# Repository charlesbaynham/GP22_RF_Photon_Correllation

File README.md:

README
======

This is the source code for the driver for the GP22 TDC chip eval board, programmed by Charles Baynham.

It is written in c++ and can be compiled and uploaded via the Arduino IDE. This code is intended to run on an Arduino Due (or other 3.3V Arduino board) to act as an interface to the GP22. When running, the Arduino will setup the GP22 with whatever configuration is stored in the GP22's EEPROM then wait for simple commands. 

N.B. The configuration of the GP22 is done via the software interface provided on http://ACAM.de. In particular, be cautious of the DELVAL1 setting in "Ultrasonic Time of Flight". This setting should be zero, but isn't by default. If not corrected, this will greatly limit the resolution of the device. 

_IMPORTANT_
-----------

If you loaded this from the T: drive you may not have the latest version. This directory is a GIT repository and so contains a hidden folder called `.git` that has a record of every change made to this code since conception. In order to use this you must install a git client. https://windows.github.com/ is a simple one or http://www.sourcetreeapp.com/ is more full-featured. 

Once installed, "checkout" the master branch for the latest code version.

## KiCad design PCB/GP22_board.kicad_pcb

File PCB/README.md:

NPL Backplane
=============

Usage
-----

_This is a Kicad Template: this whole folder should be copied into your "...\Documents\kicad\template\" folder. It can then be used be starting a new Kicad project with the "New Project from Template (Ctrl+T)" option._

Child board template - v1.0
---------------------------

This project template is designed for projects intending to use the NPL backplane system.

The NPL backplane supports 100x100mm boards and provides various supply voltages, as well as 30 GPIO ports and an interface for RS485 - serial communication. Protocol implementation is outside the scope of this document, but the Modbus protocol is recommended.

Power lines are not guaranteed to be quiet so noise-senstive applications should implement their own filtering or use an external supply. Maximum current draw is t.b.c. but other than the +15V supply line, other power supplies are expected to be relatively low current; intended for powering signal circuits only.

For more information, please contact Charles Baynham

(c) 2016 Charles Baynham

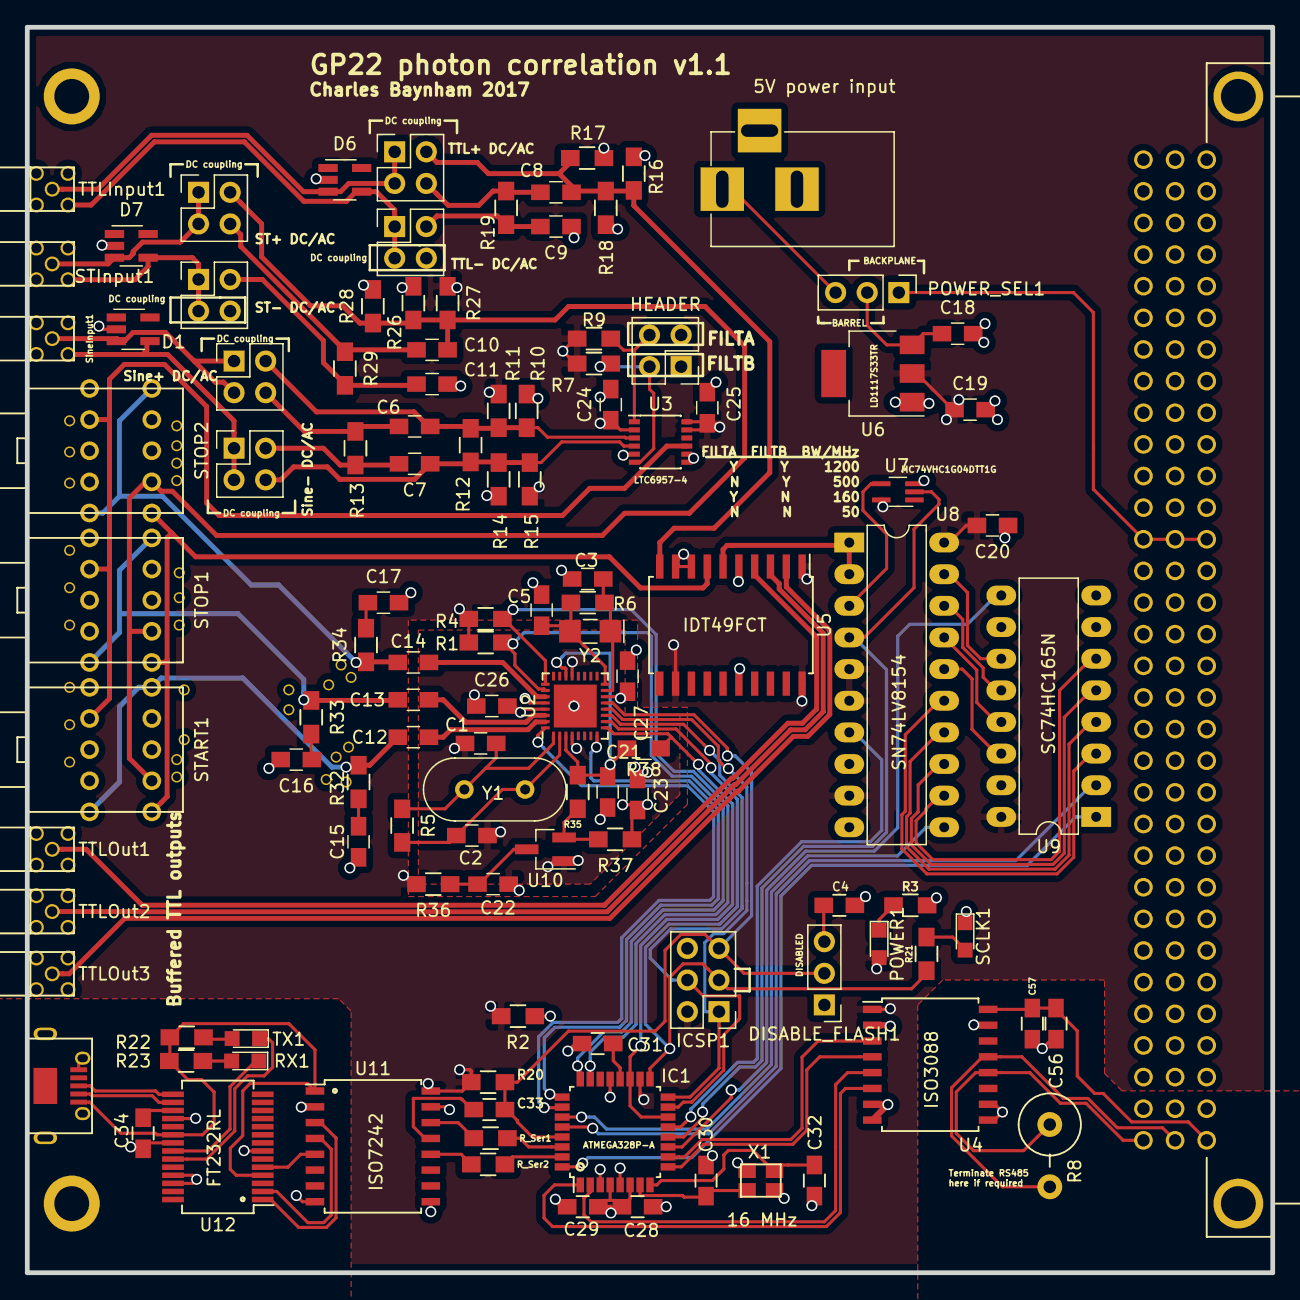
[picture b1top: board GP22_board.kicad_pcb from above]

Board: 4 copper layers, 100.0 x 100.0 mm, 145 parts (0 on the bottom side), 108 nets.

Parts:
C1, C2, C3, C5: 3p3; C_0805_HandSoldering
C4, C18, C28, C56: 1u; C_0805_HandSoldering
C6, C7, C8, C9, C10, C11: C_Small; C_0805_HandSoldering
C12, C13, C14: 10n; C_0805_HandSoldering
C15, C16, C17: x; C_0805_HandSoldering
C19: 10u; C_0805_HandSoldering
C20, C24, C25, C26, C27, C29, C31, C33, C34, C57: 100n; C_0805_HandSoldering
C21, C23: 33u; C_0805_HandSoldering
C22: 4u7; C_0805_HandSoldering
C30, C32: 8p; C_0805_HandSoldering
CON1: 5V power input; BARREL_JACK
D1, D6, D7: ESDA5V3SC6; SOT-23-5_HandSoldering
DISABLE_FLASH1: JMP; Pin_Header_Straight_1x03_Pitch2.54mm
FILT_SEL1: HEADER; Pin_Header_Straight_2x02_Pitch2.54mm
IC1: ATMEGA328P-A; LQFP-32_7x7mm_Pitch0.8mm
ICSP1: HEADER; Pin_Header_Straight_2x03_Pitch2.54mm
P4: USB_OTG; MICRO-B_USB_TOP_MOUNT
P7, P8, P9, P10, P11, P12: HEADER; Pin_Header_Straight_2x02_Pitch2.54mm
POWER1: LED; LED_0805
POWER_SEL1: JMP; Pin_Header_Straight_1x03_Pitch2.54mm
R1, R2, R4: 2M; R_0805_HandSoldering
R3, R21, R22, R23: 100R; R_0805_HandSoldering
R5: 1M; R_0805_HandSoldering
R6: x; R_0805_HandSoldering
R7, R9: 100k; R_0805_HandSoldering
R8: RS485_TERM; Resistor_Vertical_RM5mm
R10, R11, R14, R15, R16, R17, R26, R27, R38: 10k; R_0805_HandSoldering
R12, R13, R18, R19, R28, R29, R32, R33, R34: 50R; R_0805_HandSoldering
R20, R36: 1k; R_0805_HandSoldering
R35, R37: 22R; R_0805_HandSoldering
RX1: LED; LED_0805
R_Ser1, R_Ser2: 1k; R_0805_HandSoldering
SCLK1: LED; LED_0805
START1: DP3T; ALPS_Rotary_SRBM
STInput1: MMCX; MMCX_Socket
STOP1, STOP2: DP3T; ALPS_Rotary_SRBM
SineInput1: MMCX; MMCX_Socket
TTLInput1: MMCX; MMCX_Socket
TTLOut1, TTLOut2, TTLOut3: MMCX; MMCX_Socket
TX1: LED; LED_0805
U1: Right Angle; 96way_DIN_41612
U2: GP22; QFN-32-1EP_5x5mm_Pitch0.5mm
U3: LTC6957-4; MSOP-12_3x4mm_Pitch0.65mm
U4: ISO3088; SOIC-16W_7.5x10.3mm_Pitch1.27mm
U5: IDT49FCT; SOIC-20W_7.5x12.8mm_Pitch1.27mm
U6: LD1117S33TR; SOT-223
U7: MC74VHC1G04DTT1G; SOT-353_SC-70-5_Handsoldering
U8: SN74LV8154; DIP-20_W7.62mm_LongPads
U9: SC74HC165N; DIP-16_W7.62mm_LongPads
U10: XC6206; SOT-23_Handsoldering
U11: ISO7242; SOIC-16_7.5x10.3mm_Pitch1.27mm
U12: FT232RL; SSOP-28_5.3x10.2mm_Pitch0.65mm
VIA**: ViaHack
VIA**#2, VIA**#3, VIA**#4, VIA**#5, VIA**#6, VIA**#7, VIA**#8, VIA**#9, VIA**#10, VIA**#11, VIA**#12, VIA**#13, VIA**#14, VIA**#15, VIA**#16, VIA**#17, VIA**#18, VIA**#19, VIA**#20, VIA**#21, VIA**#22, VIA**#23, VIA**#24, VIA**#25, VIA**#26, VIA**#27, VIA**#28, VIA**#29: ViaHack
X1: TSX-3225 X1E0000210013; crystal_FA238-TSX3225
Y1: 4MHz; Crystal_HC49-4H_Vertical
Y2: 32.768 kHz; Crystal_SMD_MicroCrystal_CC7V-T1A-2pin_3.2x1.5mm_HandSolder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

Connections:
+3V3: C19.1, C20.2, C24.1, C25.1, C28.1, C29.1, IC1.4, IC1.6, IC1.18, ICSP1.2, POWER1.2, R1.1, R2.2, R4.1, R7.2, R9.1, R11.1, R15.2, R17.1, R20.1, R27.1, R36.2, U3.2, U3.11, U3.12, U4.1, U5.1, U5.12, U5.20, U6.2, U7.5, U8.5, U8.6, U8.9, U8.20, U9.16, U11.16
/ARD_RST: C33.1, DISABLE_FLASH1.2, IC1.29, ICSP1.5, R20.2, U2.13
/BPSubsheet/+3.3V: U1.A15, U1.B15, U1.C15
/BPSubsheet/+12V: U1.A9, U1.B9, U1.C9
/BPSubsheet/+15V: U1.A5, U1.B5, U1.C5
/BPSubsheet/+24V: U1.A1, U1.B1, U1.C1
/BPSubsheet/-5V: U1.A11, U1.B11, U1.C11
/BPSubsheet/-12V: U1.A7, U1.B7, U1.C7
/BPSubsheet/-15V: U1.A3, U1.B3, U1.C3
/Backplane_5V: POWER_SEL1.1, U1.A13, U1.B13, U1.C13
/CTR_BIT_SEL: IC1.12, U7.2, U8.4
/CTR_LOAD: IC1.13, U8.7
/Counter/~CTR_GAL: U7.4, U8.3
/DIYino/D0/RX: IC1.30, R_Ser1.1
/DIYino/D1/TX: IC1.31, R_Ser2.2
/DIYino/RX: R_Ser1.2, U11.14
/DIYino/TX: R_Ser2.1, U11.12
/DIYino/USB_3V3: C34.1, U12.17
/DIYino/USB_5V: P4.1, R22.2, R23.2, U11.1, U12.4, U12.20
/DIYino/USB_D+: P4.3, U12.15
/DIYino/USB_D-: P4.2, U12.16
/DIYino/USB_GND: C34.2, P4.5, P4.6, U11.2, U11.8, U12.7, U12.18, U12.21, U12.25, U12.26
/DIYino/USB_RESET_IN: U11.4, U12.2
/DIYino/USB_RESET_OUT: C33.2, U11.13
/G1: C12.2, U2.31
/G2: C13.2, U2.30
/G3: C14.2, U2.27
/GP22_CS: IC1.14, IC1.19, R38.1, U2.9
/GP22_EN_START: IC1.26, R2.1, U2.32
/GP22_EN_STOP1: IC1.24, R1.2, U2.26
/GP22_EN_STOP2: IC1.23, R4.2, U2.25
/GP22_INT: IC1.25, U2.8
/GP22_MISO: IC1.16, ICSP1.1, U2.12
/GP22_MOSI: IC1.15, ICSP1.4, U2.11
/GP22_SCK: IC1.17, ICSP1.3, R21.1, U2.10
/GP22_START: C12.1, R32.1, START1.1a, START1.5b
/GP22_STOP1: C13.1, R33.1, STOP1.1a, STOP1.5b
/GP22_STOP2: C14.1, R34.1, STOP2.1a, STOP2.5b
/GP22_VCC: C23.1, C26.2, C27.2, R37.1, U2.14, U2.29
/GP22_VIO: C21.1, R35.1, R38.2, U2.3, U2.22
/InputCoupling2/InputGnd: D6.4, P10.1, P10.3, TTLInput1.2
/InputCoupling2/InputSignal: D6.3, P9.1, P9.3, TTLInput1.1
/InputCoupling2/OutputS+: C8.2, P9.2, R16.1, R17.2, R18.1, U5.10
/InputCoupling2/RF_2: C8.1, P9.4, R19.1
/InputCoupling2/RF_4: C9.2, P10.2, R19.2
/InputCoupling3/InputGnd: D7.4, P12.1, P12.3, STInput1.2
/InputCoupling3/InputSignal: D7.3, P11.1, P11.3, STInput1.1
/InputCoupling3/RF_2: C10.1, P11.4, R29.1
/InputCoupling3/RF_4: C11.2, P12.2, R29.2
/InputCoupling/InputGnd: D1.4, P8.1, P8.3, SineInput1.2
/InputCoupling/InputSignal: D1.3, P7.1, P7.3, SineInput1.1
/InputCoupling/OutputS+: C6.2, P7.2, R10.1, R11.2, R12.1, U3.3
/InputCoupling/OutputS-: C7.1, P8.4, R12.2, R14.2, R15.1, U3.4
/InputCoupling/RF_2: C6.1, P7.4, R13.1
/InputCoupling/RF_4: C7.2, P8.2, R13.2
/REG_CLK: IC1.28, U9.2
/REG_DATA: IC1.11, U9.9
/REG_LOAD: IC1.32, U9.1
/RS485_+5V: C56.1, C57.1, U1.C32, U4.16
/RS485_A: R8.1, U1.A32, U4.12
/RS485_B: R8.2, U1.B32, U4.13
/RS485_D: IC1.1, U4.6
/RS485_DE: IC1.2, U4.5
/RS485_GND: C56.2, C57.2, U1.A31, U1.B31, U1.C31, U4.9, U4.10, U4.15
/RS485_R: IC1.10, U4.3
/RS485_RE: IC1.9, U4.4
/SineRectified: START1.4a, STOP1.4a, STOP2.4a, U3.9
/StraightThrough: C10.2, P11.2, R26.1, R27.2, R28.1, START1.2b, STOP1.2b, STOP2.2b
/TTLBuffered: START1.1b, STOP1.1b, STOP2.1b, U5.7
/TTLBufferedOut1: TTLOut1.1, U5.4
/TTLBufferedOut2: TTLOut2.1, U5.3
/TTLBufferedOut3: TTLOut3.1, U5.2
/TTLBufferedOut_toCounter: U5.6, U8.1, U8.2
/~CTR_CLR: IC1.27, U8.11
GND: C1.1, C2.1, C3.2, C4.2, C5.2, C9.1, C11.1, C15.2, C16.2, C17.2, C18.2, C19.2, C20.1, C21.2, C22.2, C23.2, C24.2, C25.2, C26.1, C27.1, C28.2, C29.2, C30.1, C31.2, C32.2, CON1.2, CON1.3, D1.2, D6.2, D7.2, FILT_SEL1.1, FILT_SEL1.3, IC1.3, IC1.5, IC1.21, ICSP1.6, P10.4, P12.4, R3.2, R10.2, R14.1, R16.2, R18.2, R26.2, R28.2, SCLK1.1, TTLOut1.2, TTLOut2.2, TTLOut3.2, U1.A2, U1.A4, U1.A6, U1.A8, U1.A10, U1.A12, U1.A14, U1.A16, U1.B2, U1.B4, U1.B6, U1.B8, U1.B10, U1.B12, U1.B14, U1.B16, U1.C2, U1.C4, U1.C6, U1.C8, U1.C10, U1.C12, U1.C14, U1.C16, U2.4, U2.21, U2.28, U2.33, U3.5, U3.7, U3.8, U4.2, U4.7, U4.8, U5.5, U5.8, U5.9, U5.16, U6.1, U7.3, U8.10, U9.8, U9.10, U9.15, U10.1, U11.9, U11.15, VIA**.1, VIA**#2.1, VIA**#3.1, VIA**#4.1, VIA**#5.1, VIA**#6.1, VIA**#7.1, VIA**#8.1, VIA**#9.1, VIA**#10.1, VIA**#11.1, VIA**#12.1, VIA**#13.1, VIA**#14.1, VIA**#15.1, VIA**#16.1, VIA**#17.1, VIA**#18.1, VIA**#19.1, VIA**#20.1, VIA**#21.1, VIA**#22.1, VIA**#23.1, VIA**#24.1, VIA**#25.1, VIA**#26.1, VIA**#27.1, VIA**#28.1, VIA**#29.1, X1.3
unnamed: C1.2, R5.1, U2.1, Y1.2
unnamed: C2.2, R5.2, U2.2, Y1.1
unnamed: C3.1, R6.2, U2.15, Y2.1
unnamed: C4.1, DISABLE_FLASH1.3
unnamed: C5.1, R6.1, U2.16, Y2.2
unnamed: C15.1, R32.2
unnamed: C16.1, R33.2
unnamed: C17.1, R34.2
unnamed: C18.1, POWER_SEL1.2, U6.3
unnamed: C22.1, R36.1, U10.3
unnamed: C30.2, IC1.7, X1.1
unnamed: C31.1, IC1.20
unnamed: C32.1, IC1.8, X1.2
unnamed: CON1.1, POWER_SEL1.3
unnamed: FILT_SEL1.2, R7.1, U3.6
unnamed: FILT_SEL1.4, R9.2, U3.1
unnamed: POWER1.1, R3.1
unnamed: R21.2, SCLK1.2
unnamed: R22.1, TX1.2
unnamed: R23.1, RX1.2
unnamed: R35.2, R37.2, U10.2
unnamed: RX1.1, U12.22
unnamed: TX1.1, U12.23
unnamed: U8.12, U9.6
unnamed: U8.13, U9.5
unnamed: U8.14, U9.4
unnamed: U8.15, U9.3
unnamed: U8.16, U9.14
unnamed: U8.17, U9.13
unnamed: U8.18, U9.12
unnamed: U8.19, U9.11
unnamed: U11.3, U12.1
unnamed: U11.5, U12.5

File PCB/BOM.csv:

Refs,Value,Footprint,Quantity,MFR,MPN,SPR,SPN
R9;R7,100k,Resistors_SMD:R_0805_HandSoldering,2,-,-,-,-
R8,RS485_TERM,Resistors_ThroughHole:Resistor_Vertical_RM5mm,1,-,-,-,-
R5;R6,R,Resistors_SMD:R_0805_HandSoldering,2,-,-,-,-
R38;R27;R26;R31;R30;R27;R26;R31;R30;R27;R26;R31;R30,10k,Resistors_SMD:R_0805_HandSoldering,13,-,-,-,-
R35;R37,22R,Resistors_SMD:R_0805_HandSoldering,2,-,-,-,-
R32;R33;R34;R29;R28;R29;R28;R29;R28,50R,Resistors_SMD:R_0805_HandSoldering,9,-,-,-,-
R21;R22;R23;R3,100R,Resistors_SMD:R_0805_HandSoldering,4,-,-,-,-
R20;R_Ser1;R_Ser2;R36,1k,Resistors_SMD:R_0805_HandSoldering,4,-,-,-,-
R2;R1;R4,2M,Resistors_SMD:R_0805_HandSoldering,3,-,-,-,-
C31;C29;C33;C34;C57;C24;C25;C26;C27;C20,100n,Capacitors_SMD:C_0805_HandSoldering,10,-,-,-,-
C30;C32,8p,Capacitors_SMD:C_0805_HandSoldering,2,-,-,-,-
C28;C4;C56;C18,1u,Capacitors_SMD:C_0805_HandSoldering,4,-,-,-,-
C22,4u7,Capacitors_SMD:C_0805_HandSoldering,1,-,-,-,-
C21;C23,33u,Capacitors_SMD:C_0805_HandSoldering,2,-,-,-,-
C19,10u,Capacitors_SMD:C_0805_HandSoldering,1,-,-,-,-
C15;C16;C17,10p,Capacitors_SMD:C_0805_HandSoldering,3,-,-,-,-
C12;C13;C14,10n,Capacitors_SMD:C_0805_HandSoldering,3,-,-,-,-
C10;C11;C10;C11;C10;C11,C_Small,Capacitors_SMD:C_0805_HandSoldering,6,-,-,-,-
C1;C2;C5;C3,C,Capacitors_SMD:C_0805_HandSoldering,4,-,-,-,-
U2,GP22,Housings_DFN_QFN:QFN-32-1EP_5x5mm_Pitch0.5mm,1,ACAM,TDC-GP22,Digikey,TDC-GP225KT&RCT-ND
START1;STOP1;STOP2,DP3T,Custom:ALPS_Rotary_SRBM,3,Apls Electric,SRBM131400,RS,123-9600
SCLK1;TX1;RX1;POWER1,LED,LEDs:LED_0805,4,Bivar,SM0805HC,RS,147-9844
X1,TSX-3225 X1E0000210013,Crystals:crystal_FA238-TSX3225,1,Epson,X1E000021001311,RS,667-6151
U12,FT232RL,Housings_SSOP:SSOP-28_5.3x10.2mm_Pitch0.65mm,1,FTDI Chip,FT232RL,RS,406-580
ICSP1,HEADER,Pin_Headers:Pin_Header_Straight_2x03_Pitch2.54mm,1,Harwin,M20-9980346,RS,745-7046
U5,IDT49FCT,Housings_SOIC:SOIC-20W_7.5x12.8mm_Pitch1.27mm,1,IDT,IDT49FCT3805ASOGI,RS,715-4902
U3,LTC6957-4,Housings_SSOP:MSOP-12_3x4mm_Pitch0.65mm,1,Linear,LTC6957-4,Digikey,DC1766A-B-ND
Y1,4MHz,Crystals:Crystal_HC49-4H_Vertical,1,Mercury,H49-4.000-18-30/50/4085,RS,672-0173
Y2,32.768 kHz,Crystals:Crystal_SMD_MicroCrystal_CC7V-T1A-2pin_3.2x1.5mm_HandSoldering,1,Micro Crystal,CM7V-T1A 32.768kHz 7pF +/-10ppm TA QC,RS,729-3252
IC1,ATMEGA328P-A,Housings_QFP:LQFP-32_7x7mm_Pitch0.8mm,1,Microchip Technology,ATMEGA328P-AN,RS,131-0270
SineInput1;TTLInput1;STInput1;TTLOut1;TTLOut2;TTLOut3,MMCX,Custom:MMCX_Socket,6,Molex,73415-1001,RS,759-5300
P4,USB_OTG,Custom:MICRO-B_USB_TOP_MOUNT,1,Molex,47590-0001,RS,702-5481
U7,MC74VHC1G04DTT1G,TO_SOT_Packages_SMD:SOT-353_SC-70-5_Handsoldering,1,ON Semiconductor,MC74VHC1G04DTT1G,RS,806-3964
U1,Right Angle,Backplane:96way_DIN_41612,1,RS Pro,252-210,RS,252-210
DISABLE_FLASH1;POWER_SEL1,JMP,Pin_Headers:Pin_Header_Straight_1x03_Pitch2.54mm,2,RS Pro,251-8092,RS,251-8092
U6,LD1117S33TR,TO_SOT_Packages_SMD:SOT-223,1,STMicroelectroncs,LD1117S33TR,RS,168-6804
D7;D7;D7,ESDA5V3SC6,TO_SOT_Packages_SMD:SOT-23-5_HandSoldering,3,STMicroelectronics,ESDA5V3SC6,RS,102-6170
CON1,5V power input,Connect:BARREL_JACK,1,Switchcraft,RAPC712X,RS,878-6787
FILT_SEL1;S+ DC/AC;S- DC/AC;S+ DC/AC;S- DC/AC;S+ DC/AC;S- DC/AC,HEADER,Pin_Headers:Pin_Header_Straight_2x02_Pitch2.54mm,7,TE Connectivity,826632-2,RS,669-5288
U9,SC74HC165N,Housings_DIP:DIP-16_W7.62mm_LongPads,1,TI,SN74HC165N,RS,333-2978
U8,SN74LV8154,Housings_DIP:DIP-20_W7.62mm_LongPads,1,TI,SN74LV8154PW,RS,663-2782
U4,ISO3088,Housings_SOIC:SOIC-16W_7.5x10.3mm_Pitch1.27mm,1,TI,ISO3088DW,RS,121-9061
U11,ISO7242,Housings_SOIC:SOIC-16_7.5x10.3mm_Pitch1.27mm,1,TI,ISO7242CDW,RS,121-9145
U10,XC6206,TO_SOT_Packages_SMD:SOT-23_Handsoldering,1,Torex,XC6206P332PR,Farnell,8796998

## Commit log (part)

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2015-02-25 Formatting
2015-02-25 Rewrite into driver
2015-02-25 Null char to terminate command str
2015-02-25 Convention
2015-02-25 Typo
2015-02-25 Timing bug
2015-02-25 No hardcoding allowed
2015-02-25 Read the params more safely
2015-02-25 Report data as spreadsheet string
2015-02-26 Trying to debug
2015-02-26 Do EEPROM load in the arduino init rather than before each measurement
2015-02-26 Add single measurement mode
2015-02-26 Add proj files
2015-03-12 Consolidate labview versions into only the 2013 version
2015-03-12 Commenting
2015-03-12 Read status
2015-03-12 Function to write the config
2015-03-12 Clarify the output of the calibration routine
2015-03-13 Test function was returning false positives
2015-03-13 Add a setup command
2015-03-13 Add labview interface to setup the TDC known registers
2015-03-13 Make arduino aware of which mode it's in and report data accordingly (16 bits or 32 bits depending on calibration settings)
2015-03-13 Update labview to recognise and compensate for uncalibrated data
2015-03-13 Scrap the "DONE" after measurements
2015-03-13 Avoid the 0 measurements at the start and end by trimming the string first
2015-03-13 Labview interface to setup defaults, read uncalibrated data and test for the calibration wobble
2015-03-16 Use the ACAM sequence for calibration but read the pointer from STATUS N.B. These calibration measurements seem to loop very predictably. I think this is the TDC, not my code
2015-03-16 Check status before reading calibration
2015-03-16 Go into MM2 and use quad resolution for the calibration
2015-03-17 Move the init for calibration to before the calculation requests since the START_TDC_CAL actually produces hits. Also update Labview to reflect corrected calibration.
2015-03-17 Labview state machine for examples
2015-03-17 Fix odd ordering of calibration in single measurement
2015-03-18 Change histogram defaults to cover a cold start of the oscillator
2015-03-20 Histogram dynamically updates while data comes in
2015-03-20 Labview: histogram changes for the time measurements too
2015-03-20 Histogram changes
2015-03-20 Read_bytes function
2015-03-20 Store all registers on the arduino
2015-03-20 Labview: High freq calibration method
2015-03-20 Labview: Proj updates
2015-03-20 Update globals
2015-03-20 Integrate calibrated clock into all VIs
2015-03-20 Add calibration to the state machine
2015-03-20 Progress bar for measurements
2015-03-20 Add configuration options for double precision / auto-calibrate
2015-03-31 Adapt for new breakout board
2015-03-31 Much commenting and graph adjustments
2015-03-31 Bump version
2015-05-07 Various changes, mostly GUI and config registers
2015-05-07 Add blank VI for outputting binned timing data
2015-05-07 Rename MeasureMode2 -> MultipleMeasurements since this is what it actually does
2015-05-07 Use new subVI for multiple measurements
2015-05-07 Show this VI when it's called as a subVI, then close it again
2015-05-07 Return data, binned properly and using new function
2015-05-07 Clarify labels
2015-05-07 Documentation and trimming useless stuff
2015-05-07 Write wrapper to convert data exactly to old format
2015-05-07 Set TDC to measure difference between STOP1 and START (for actual RF timing)
2015-09-08 Setup GP22 with the default config on init (as oposed to reloading from EEPROM)
2016-05-11 Adapt for AtMega328P usage
2016-05-12 Fix various bugs
2016-05-12 Update and minor changes
2016-05-12 Rename function
2016-05-12 Add CommandHandler as submodule
2016-05-12 Start using commandHandler
2016-05-12 Write most functions in CommandHandler's format
2016-05-12 Pass String objects for parameters
2016-05-12 Typos
2016-05-12 Load registers command
2016-05-13 Part qway through debug
2016-05-13 Remove hashmap
2016-05-13 Use List<String> instead of Vector<String>
2016-05-13 Ignore Visual Studio files
2016-05-13 Basic MWE of error
2016-05-13 Format list debug
2016-05-13 Debug command for handler
2016-05-13 Output list debug every cycle
2016-05-23 Fix memory leak
    Fix memory leak, check for too long commands better. Also improve
    debugging by adding macros and more useful messages
2016-05-23 Found and fixed the problem!
2016-05-23 Bug in debugging code
2016-05-23 Various whopsies
2016-05-23 ListItem as a private child class
2016-05-23 Template for iterators
2016-05-23 Do away with basicVector
2016-05-23 Iterators for Lists
2016-05-23 STILL a mem leak!
2016-05-23 Restore basicVector (though don't use it since actually a list is better)
2016-05-23 Found a really silly mem leak
2016-05-23 Logging
2016-05-23 Code trimming
2016-05-23 Found it!
    This one is fun. So the List I made is being implicitly copied, but its destructor `delete`s its ListItems when one instance is destructed, leaving the other with invalid pointers. To fix this I shou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
    a) Write a proper copy constructor. This wastes loads of memory
    b) Implement const methods to prevent this from happening
2016-05-23 Try to start const_iterators
2016-05-23 Implement const iterators and also disable the copy constructor until I've made a safe one
2016-05-24 Working const Iterators. Use base class Iterator_base and return const references
2016-05-24 Also allow return of non-const references for the normal Iterators
2016-05-24 Test const and non-const iterators
2016-05-24 Loop testing list ad infinitum
2016-05-24 Better debugging
2016-05-24 Avoid copying Lists
2016-06-09 Much smarter vector structure
2016-06-14 Add unique_ptr
2016-06-14 Define assignment for unique_ptr
2016-06-20 Add pointer dereferencing and a make_shared function
2016-06-20 Add a make_unique function too
2016-06-20 Const getter
2016-06-22 Don't bother differentiating queries
2016-06-22 Debug and formatting
2016-06-22 Fix HORRIBLE bug
    Seriously, this one took me two days to find
2016-06-22 Disable debugging
2016-06-27 Error handling varargin
2016-06-29 Add debugging submodule and use
2016-06-29 In debugging mode, output warnings for false dereferencing
2016-07-01 Tested store, retrieve,clear
2016-07-01 Tested queue. Automatically add the stored command to the queue as soon as the CommandHandler is constucted
2016-07-01 Add EEPROM example
2016-07-01 Add BasicUsage example
2016-07-01 Accept semicolons but introduce bizarre bug
2016-07-01 Fix (but not understand) weird bug
2016-07-01 Add newline to stored commands since we delimit commands with ';' now
2016-07-01 Debugging logs
2016-07-01 Don't accept semicolons in normal commands: only in EEPROM calls
2016-07-01 Rename Iterator and Iterator_const to iterator and const_iterator, inline with std
2016-07-01 Debugging
2016-07-04 Store shared_ptrs of Strings
2016-07-04 Store hashes of strings instead of actual strings
2016-07-05 Structure for new stack based commandHandler (not working yet)
2016-07-05 Auto indent
2016-07-05 Full stack CommandHandler!
2016-07-05 Fix newly broken EEPROM functionality
2016-07-05 Debugging line
2016-07-05 Update EEPROM example
2016-07-05 Shared_ptr_d bug
2016-07-05 Fully stack based CommandHandler
    Also uses hashes intead of strings for storage. This class uses dramatically less memory
2016-07-05 Update examples
2016-07-05 Move it all into a template
2016-07-05 Update example 2
2016-07-06 Return ExecuteError from executeStartupCommands
2016-07-07 Add dump() function to CommandHandler for debugging
2016-07-07 BUG: Check for Serial comms before outputting
2016-07-07 Use explicit operator bool() for safety
2016-07-08 Rename enum
2016-07-11 Use stack only version of CommandHandler
2016-07-11 Use T drive git repos
2016-07-11 Bug in setting registers
2016-07-15 Intial commit
2016-07-15 GP22 register enums
2016-07-15 Comments
2016-07-15 Test it works. It does!
2016-07-18 Lots of comments
2016-07-18 Align
2016-07-26 Comments and explicit size
2016-07-28 BUGFIX: ssending register settings failed if the first bit was high
2016-07-28 Add test_data bitmask
2016-07-28 Indent
2016-07-28 First attempt at histogram function
2016-07-29 Update project files
2016-08-24 Dump the Vectors and Lists: heap allocation is dangerous in a limited-memory environement
2016-09-20 Use enum class instead of enum
2016-09-20 Update examples for new enum classes
2016-10-10 Add Doxygen todo
2016-10-21 Be a bit less memory hungry:
    Avoid Strings and don't request MAX_COMMAND_SIZE buffers from the stack other than the preassigned one
2016-11-03 Expand CommandHandler memory space
2016-11-03 Fix typo
2016-11-03 Use fixed register access
2016-11-04 Use default config to begin with, then change registers with commands. Also read measurements as signed, assuming measurement mode 1
2016-11-04 Convert to SI units
2016-11-04 Allow min value for histogram
2016-11-04 Go to double res mode when possible
2016-11-04 Add not-working photon-photon mode and debugging stuff
2017-01-31 NPL Backplane template initial commit
2017-01-31 Add GP22 schematic
2017-02-03 Sketch
2017-02-03 Inputs designed
2017-02-09 Nearly finish schematic, add counter, coupling options
2017-02-09 Complete (?) schematic, footprints and component selection
2017-02-09 Route the signals! And replace the diodes
2017-02-09 Board nearly done
2017-02-10 Take 5V from backplane instead of 3V3: regulate it on-board
2017-02-10 Silkscreen labelling
2017-02-10 Tweaks to RF path
2017-02-10 Flood the top and bottom
2017-02-10 Swap plane order and route power by bottom pour, for EMC and ground-inductance considerations
2017-02-10 Add soldermask to via hack, label board, gerbers
2017-02-20 BOM added
2017-02-22 Dump the annoying submodule
2017-03-01 Convenience stuff for histogram test function (this surely can be quicker!)
2017-03-01 Update to latest CommandHandler (uses hashes instead of stored strings)
2017-03-01 Timeout warning for calibration
2017-03-03 Error checking
2017-03-13 Add Solidworks frontpanel
2017-03-13 Save changes to panel and output as STL
2017-03-21 Correct stack overflow error and report command_roo_long errors
2017-07-20 Re-add microprocessor debugging
2017-07-20 Add hooks
2017-07-20 Bring in Labview changes from v2017 on Fara
2017-07-20 Speed up SPI comms
2017-07-20 Labview getting there
2017-07-20 Multiple measurement mode listens to calibration, device starts at defaults + double res, mode 1
2017-07-21 Labview works
2017-07-24 Labview working
2017-07-24 Move, since it's no longer a 2013 version
2017-07-26 Add "STAT?" as an option
2017-07-26 Bring in Labview changes from MicromotionMinimiser
2017-09-27 Rename code dir
2018-06-28 Update sch for new kicad version
2018-06-28 Ground crystal case
2018-06-28 Correct input coupling orientation
2018-06-28 Record the part number of the rotary switch
2018-06-28 Fix the Rotary switch schematic file
2018-06-28 Create netlist and update board: no changes except to crystal grounding
2018-08-08 Produce BOM with "Boms away"
2018-08-08 Labelling tweaks
2018-08-08 Output gerbers
2018-08-14 Remove redundant trace spottted by Newbury
2018-09-10 Print schematic
2018-09-20 Get final cap values for BOM order with PCBTrain
2018-09-26 Correct BOM issues in schematic + update to Kicad v5.0
2018-10-05 Correct hooks
2018-10-05 Correct logic bug in calibration routine and remove unused (and impossible) method
2019-06-17 Add ability to change clock division ratio
2019-10-08 Add timed START occurrence
2019-10-08 Add to CommandHandler
2019-10-08 Report in us resolution
2019-10-08 Consistency
2019-10-08 Ignore all CLion files
2019-10-08 Compensate for TDC measurement length
2019-10-08 Rename LV dir
2019-10-08 Allow enabling fire_start
2019-10-09 Fire a start pulse in measure() if it's enabled
2019-10-09 Overflow bug
2019-10-09 Mask off overflow when setting fields
2019-10-09 Typo in reg value
2019-10-09 Typo in mask
2019-10-09 Add ability to time arrival at stop 1
2019-10-09 Fix indentation
2019-10-09 Start triggered meas
2019-10-10 Clarify HCAL behaviour
2019-10-10 Update labview with changes and fixed from NPL Time project
2019-10-11 Add 14HP panel
2019-10-17 Rack mount for 12HP
2019-11-19 Add 2017 compatibility
